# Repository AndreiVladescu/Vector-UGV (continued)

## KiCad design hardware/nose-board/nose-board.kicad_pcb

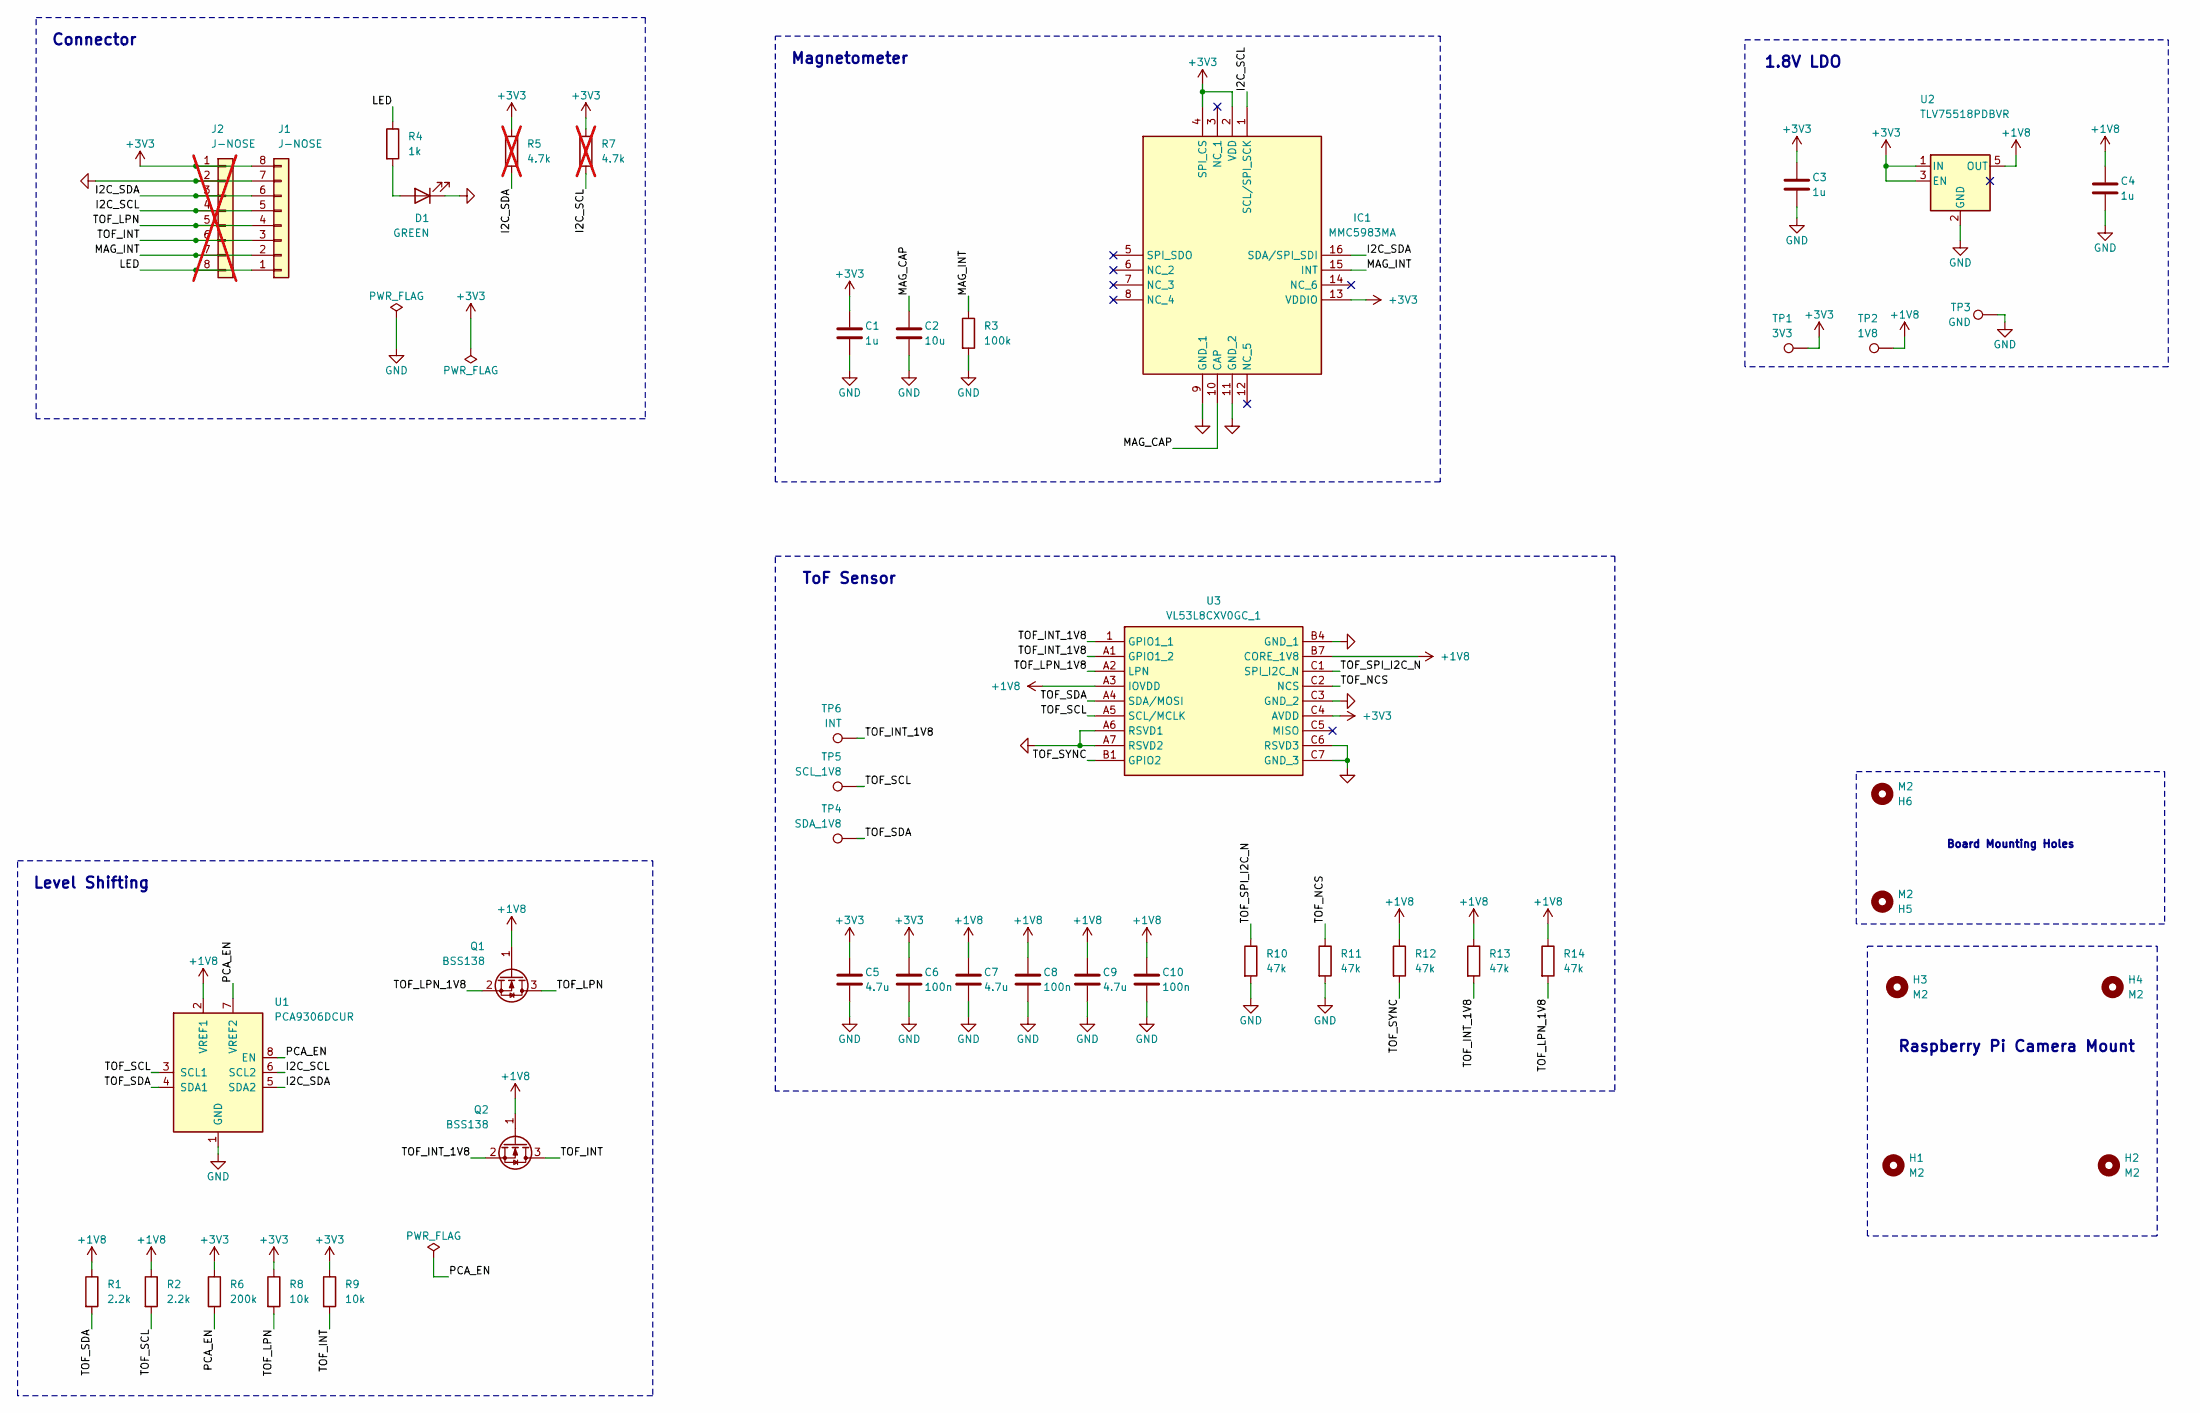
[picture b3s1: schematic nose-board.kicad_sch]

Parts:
C1, C3, C4: 1u; C_0603_1608Metric
C2: 10u; C_0805_2012Metric
C5, C7, C9: 4.7u; C_0805_2012Metric
C6, C8, C10: 100n; C_0603_1608Metric
D1: GREEN; LED_0603_1608Metric
H1, H2, H3, H4: M2; MountingHole_2.2mm_M2
H5, H6: M2; MountingHole_2.2mm_M2_Pad_TopBottom
IC1: MMC5983MA; Mouser Part Number 438-MMC5983MA
J1: J-NOSE; JST_GH_SM08B-GHS-TB_1x08-1MP_P1.25mm_Horizontal
J2: J-NOSE; JST_GH_SM08B-GHS-TB_1x08-1MP_P1.25mm_Horizontal; not fitted
Q1, Q2: BSS138; SOT-23
R1, R2: 2.2k; R_0603_1608Metric
R3: 100k; R_0603_1608Metric
R4: 1k; R_0603_1608Metric
R5, R7: 4.7k; R_0603_1608Metric; not fitted
R6: 200k; R_0603_1608Metric
R8, R9: 10k; R_0603_1608Metric
R10, R11, R12, R13, R14: 47k; R_0603_1608Metric
TP1: 3V3; TestPoint_Pad_D2.0mm
TP2: 1V8; TestPoint_Pad_D2.0mm
TP3: GND; TestPoint_Pad_D2.0mm
TP4: SDA_1V8; TestPoint_Pad_D2.0mm
TP5: SCL_1V8; TestPoint_Pad_D2.0mm
TP6: INT; TestPoint_Pad_D2.0mm
U1: PCA9306DCUR; VSSOP-8_2.3x2mm_P0.5mm
U2: TLV75518PDBVR; SOT-23-5
U3: VL53L8CXV0GC_1; VL53L8CXV0GC1; Mouser Part Number 511-VL53L8CXV0GC/1

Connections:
+1V8: C4.1, C7.1, C8.1, C9.1, C10.1, Q1.1 (G), Q2.1 (G), R1.1, R2.1, R12.1, R13.1, R14.1, TP2.1 (1_1), U1.2 (VREF1), U2.5 (OUT), U3.A3 (IOVDD), U3.B7 (CORE_1V8)
+3V3: C1.1, C3.1, C5.1, C6.1, IC1.2 (VDD), IC1.4 (SPI_CS), IC1.13 (VDDIO), J1.8, J2.1, R5.1, R6.1, R7.1, R8.1, R9.1, TP1.1 (1_1), U2.1 (IN), U2.3 (EN), U3.C4 (AVDD)
/I2C_SCL: IC1.1 (SCL/SPI_SCK), J1.5, J2.4, R7.2, U1.6 (SCL2)
/I2C_SDA: IC1.16 (SDA/SPI_SDI), J1.6, J2.3, R5.2, U1.5 (SDA2)
/LED: J1.1, J2.8, R4.1
/MAG_CAP: C2.1, IC1.10 (CAP)
/MAG_INT: IC1.15 (INT), J1.2, J2.7, R3.1
/PCA_EN: R6.2, U1.7 (VREF2), U1.8 (EN)
/TOF_INT: J1.3, J2.6, Q2.3 (D), R9.2
/TOF_INT_1V8: Q2.2 (S), R13.2, TP6.1 (1_1), U3.1 (GPIO1_1), U3.A1 (GPIO1_2)
/TOF_LPN: J1.4, J2.5, Q1.3 (D), R8.2
/TOF_LPN_1V8: Q1.2 (S), R14.2, U3.A2 (LPN)
/TOF_NCS: R11.1, U3.C2 (NCS)
/TOF_SCL: R2.2, TP5.1 (1_1), U1.3 (SCL1), U3.A5 (SCL/MCLK)
/TOF_SDA: R1.2, TP4.1 (1_1), U1.4 (SDA1), U3.A4 (SDA/MOSI)
/TOF_SPI_I2C_N: R10.1, U3.C1 (SPI_I2C_N)
/TOF_SYNC: R12.2, U3.B1 (GPIO2)
GND: C1.2, C2.2, C3.2, C4.2, C5.2, C6.2, C7.2, C8.2, C9.2, C10.2, D1.1 (K), IC1.9 (GND_1), IC1.11 (GND_2), J1.7, J2.2, R3.2, R10.2, R11.2, TP3.1 (1_1), U1.1 (GND), U2.2 (GND), U3.A6 (RSVD1), U3.A7 (RSVD2), U3.B4 (GND_1), U3.C3 (GND_2), U3.C6 (RSVD3), U3.C7 (GND_3)
unnamed: D1.2 (A), R4.2

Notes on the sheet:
Magnetometer
ToF Sensor
Board Mounting Holes
Raspberry Pi Camera Mount
Level Shifting
1.8V LDO
Connector

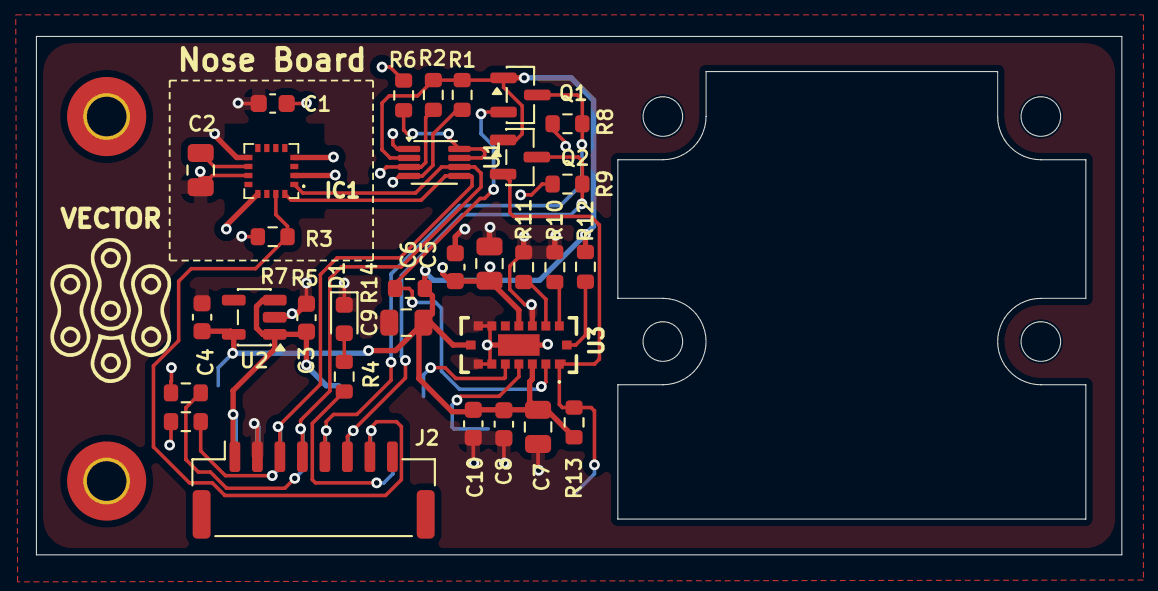
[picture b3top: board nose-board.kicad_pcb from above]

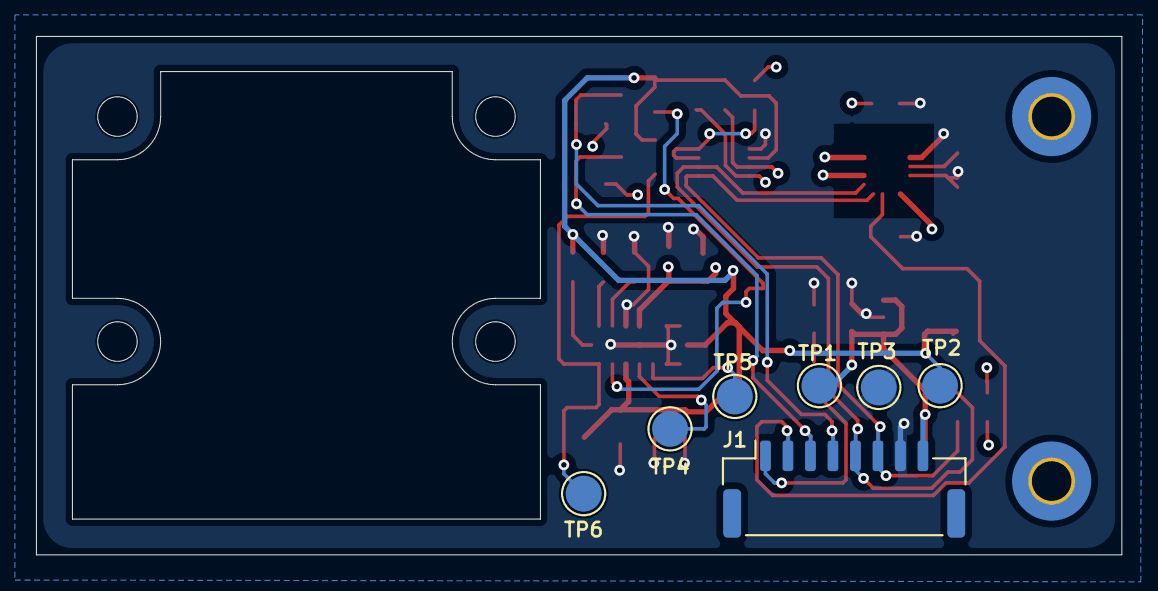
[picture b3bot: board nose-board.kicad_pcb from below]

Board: 4 copper layers, 60.3 x 28.8 mm, 45 parts (7 on the bottom side), 19 nets.

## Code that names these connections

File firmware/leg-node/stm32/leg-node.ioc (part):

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Mcu.Name=STM32C092KCTx
Mcu.Package=LQFP32
Mcu.UserName=STM32C092KCTx
PA0.GPIOParameters=GPIO_Label
PA0.GPIO_Label=ADC_POT_COXA
PA0.Mode=IN0
PA0.Signal=ADC1_IN0
PA1.GPIOParameters=GPIO_Label
PA1.GPIO_Label=ADC_POT_FEMUR
PA1.Mode=IN1
PA1.Signal=ADC1_IN1
PA10.GPIOParameters=GPIO_Label
PA10.GPIO_Label=TIM_PWM_TIBIA
PA10.Signal=S_TIM1_CH3
PA11\ [PA9].Mode=FDCAN_Activate
PA11\ [PA9].Signal=FDCAN1_RX
PA12\ [PA10].Mode=FDCAN_Activate
PA12\ [PA10].Signal=FDCAN1_TX
PA13.Mode=Serial_Wire
PA13.Signal=DEBUG_SWDIO
PA14-BOOT0.Mode=Serial_Wire
PA14-BOOT0.Signal=DEBUG_SWCLK
PA15.GPIOParameters=GPIO_Label
PA15.GPIO_Label=LED
PA15.Signal=GPIO_Output
PA2.GPIOParameters=GPIO_Label
PA2.GPIO_Label=ADC_POT_TIBIA
PA2.Mode=IN2
PA2.Signal=ADC1_IN2
PA3.GPIOParameters=GPIO_Label
PA3.GPIO_Label=ADC_I_LEG
PA3.Mode=IN3
PA3.Signal=ADC1_IN3
PA4.GPIOParameters=GPIO_Label
PA4.GPIO_Label=NTC_SENSE
PA4.Mode=IN4
PA4.Signal=ADC1_IN4
PA5.GPIOParameters=GPIO_Label
PA5.GPIO_Label=ADC_VBAT
PA5.Mode=IN5
PA5.Signal=ADC1_IN5
PA6.GPIOParameters=GPIO_Label
PA6.GPIO_Label=ADC_6V0
PA6.Mode=IN6
PA6.Signal=ADC1_IN6
PA7.GPIOParameters=GPIO_Label
PA7.GPIO_Label=DBG
PA7.Signal=GPIO_Output
PA8.GPIOParameters=GPIO_Label
PA8.GPIO_Label=TIM_PWM_COXA
PA8.Signal=S_TIM1_CH1
PA9.GPIOParameters=GPIO_Label
PA9.GPIO_Label=TIM_PWM_FEMUR
PA9.Signal=S_TIM1_CH2
PB0.GPIOParameters=GPIO_Label
PB0.GPIO_Label=BUCK_EN
PB0.Signal=GPIO_Output
PB1.GPIOParameters=GPIO_Label
PB1.GPIO_Label=BUCK_PG
PB1.Signal=GPIO_Input
PB2.GPIOParameters=GPIO_Label
PB2.GPIO_Label=GPIO_ESTOP
PB2.Signal=GPIO_Input
PB3.GPIOParameters=GPIO_PuPd,GPIO_Label
PB3.GPIO_PuPd=GPIO_PULLDOWN
PB3.GPIO_Label=LEG_ID_B0
PB3.Signal=GPIO_Input
PB4.GPIOParameters=GPIO_Label
PB4.GPIO_Label=TOF_INT
PB4.Signal=GPIO_Input
PB5.GPIOParameters=GPIO_Label
PB5.GPIO_Label=TOF_XSHUT
PB5.Signal=GPIO_Output
PB6.GPIOParameters=GPIO_Label
PB6.GPIO_Label=TOF_SCL
PB6.Mode=I2C
PB6.Signal=I2C1_SCL
PB7.GPIOParameters=GPIO_Label
PB7.GPIO_Label=TOF_SDA
PB7.Mode=I2C
PB7.Signal=I2C1_SDA
PB8.GPIOParameters=GPIO_PuPd,GPIO_Label
PB8.GPIO_PuPd=GPIO_PULLDOWN
PB8.GPIO_Label=LEG_ID_B1
PB8.Signal=GPIO_Input
PB9.GPIOParameters=GPIO_PuPd,GPIO_Label
PB9.GPIO_PuPd=GPIO_PULLDOWN
PB9.GPIO_Label=SIDE_BIT
PB9.Signal=GPIO_Input
PC14-OSCX_IN(PC14).Mode=HSE-External-Oscillator
PC14-OSCX_IN(PC14).Signal=RCC_OSCX_IN
PC15-OSCX_OUT(PC15).Mode=HSE-External-Oscillator
PC15-OSCX_OUT(PC15).Signal=RCC_OSCX_OUT
RCC.HSE_VALUE=40000000
RCC.SYSCLKFreq_VALUE=48000000
board=custom
